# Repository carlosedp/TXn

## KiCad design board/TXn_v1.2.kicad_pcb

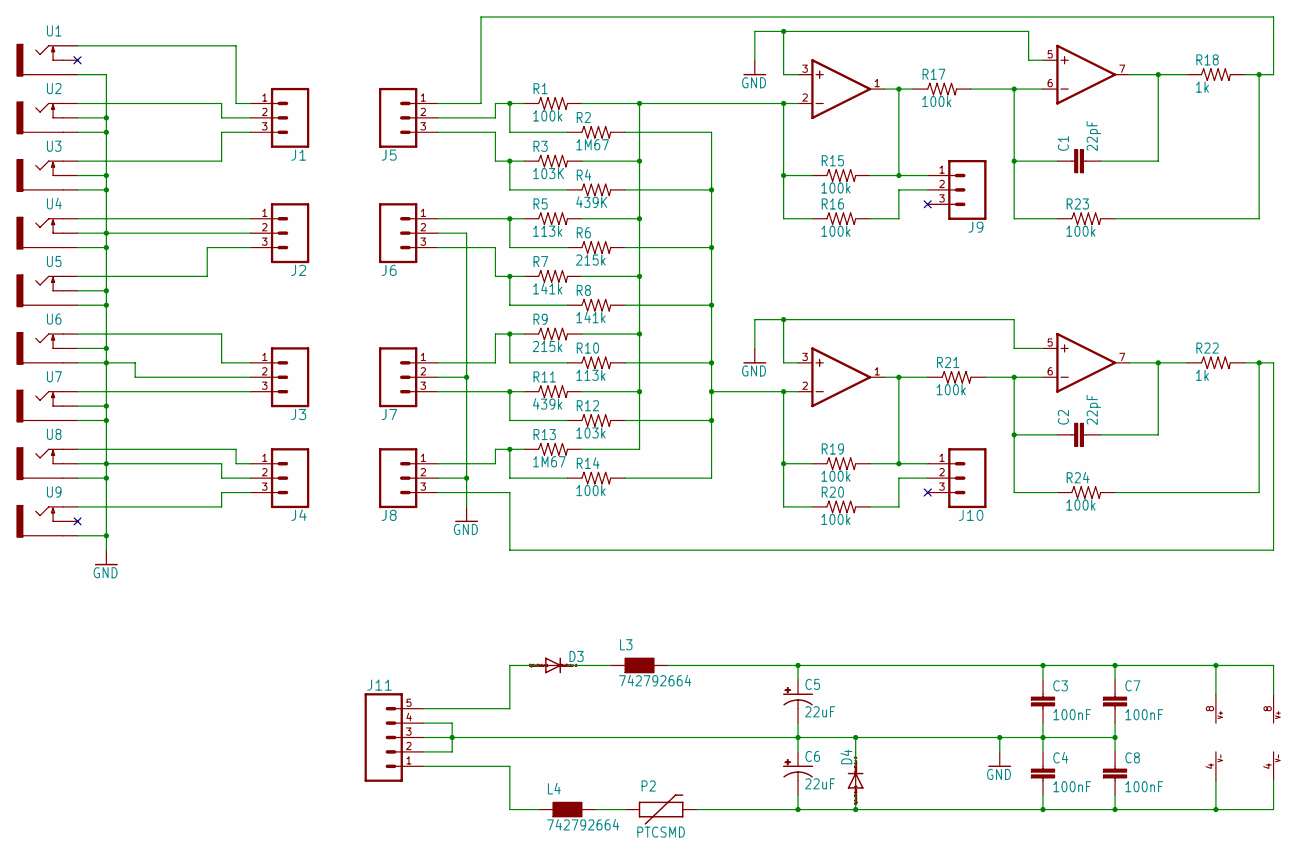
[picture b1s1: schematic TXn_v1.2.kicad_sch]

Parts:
C1, C2: 22pF; 0603-CAP
C3, C4, C7, C8: 100nF; 0603-CAP
C5, C6: 22uF; PANASONIC_B
D3, D4: DIODE-SOD123; SOD123
IC1, IC2: LME49720; SO08
J1, J2, J3, J4, J5, J6, J7, J8, J9, J10: CONN_031X03_NO_SILK; 1X03_NO_SILK
J11: CONN_05NO_SILK; 1X05_NO_SILK
L3, L4: 742792664; 0603
P2: PTCSMD; PTC-1206
R1, R14, R15, R16, R17, R19, R20, R21, R23, R24: 100k; R0603
R2, R13: 1M67; R0603
R3: 103K; R0603
R4: 439K; R0603
R5, R10: 113k; R0603
R6, R9: 215k; R0603
R7, R8: 141k; R0603
R11: 439k; R0603
R12: 103k; R0603
R18, R22: 1k; R0603
U1, U2, U3, U4, U5, U6, U7, U8, U9: THONKICONNLEFT; WQP-PJ301M-12_JACK_L

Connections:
BMIX: IC2.2 (-IN), R2.2, R4.2, R6.2, R8.2, R10.2, R12.2, R14.2, R19.1, R20.1
BOUT: J8.3, R22.2, R24.2
GND: C3.2, C4.1, C5.-, C6.+, C7.2, C8.1, D4.C, IC1.3 (+IN), IC1.5 (+IN), IC2.3 (+IN), IC2.5 (+IN), J2.2, J3.2, J4.2, J6.2, J7.2, J8.2, J11.2, J11.3, J11.4, U1.P$3_SLEEVE (SLEEVE), U2.P$2_SWITCH (SWITCH), U2.P$3_SLEEVE (SLEEVE), U3.P$2_SWITCH (SWITCH), U3.P$3_SLEEVE (SLEEVE), U4.P$2_SWITCH (SWITCH), U4.P$3_SLEEVE (SLEEVE), U5.P$2_SWITCH (SWITCH), U5.P$3_SLEEVE (SLEEVE), U6.P$2_SWITCH (SWITCH), U6.P$3_SLEEVE (SLEEVE), U7.P$2_SWITCH (SWITCH), U7.P$3_SLEEVE (SLEEVE), U8.P$2_SWITCH (SWITCH), U8.P$3_SLEEVE (SLEEVE), U9.P$3_SLEEVE (SLEEVE)
unnamed: J1.1, U1.P$1_TIP (TIP)
unnamed: J5.2, R1.1, R2.1
unnamed: J5.3, R3.1, R4.1
unnamed: J6.1, R5.1, R6.1
unnamed: J6.3, R7.1, R8.1
unnamed: J7.3, R11.1, R12.1
unnamed: J8.1, R13.1, R14.1
unnamed: J7.1, R9.1, R10.1
unnamed: J4.3, U9.P$1_TIP (TIP)
unnamed: J4.1, U8.P$1_TIP (TIP)
unnamed: J1.2, U2.P$1_TIP (TIP)
unnamed: J1.3, U3.P$1_TIP (TIP)
unnamed: J2.1, U4.P$1_TIP (TIP)
unnamed: J2.3, U5.P$1_TIP (TIP)
unnamed: J3.3, U7.P$1_TIP (TIP)
unnamed: IC2.1 (OUT), J10.1, R19.2, R21.1
unnamed: J3.1, U6.P$1_TIP (TIP)
unnamed: C2.1, IC2.6 (-IN), R21.2, R24.1
unnamed: IC1.1 (OUT), J9.1, R15.2, R17.1
unnamed: C1.1, IC1.6 (-IN), R17.2, R23.1
unnamed: C2.2, IC2.7 (OUT), R22.1
unnamed: J9.2, R16.2
unnamed: C1.2, IC1.7 (OUT), R18.1
unnamed: J10.2, R20.2
unnamed: D3.C, L3.1
unnamed: L4.2, P2.1
TMIX: IC1.2 (-IN), R1.2, R3.2, R5.2, R7.2, R9.2, R11.2, R13.2, R15.1, R16.1
TOUT: J5.1, R18.2, R23.2
VCC: C3.1, C5.+, C7.1, IC1.8 (V+), IC2.8 (V+), L3.2
VCC1: D3.A, J11.5
VEE: C4.2, C6.-, C8.2, D4.A, IC1.4 (V-), IC2.4 (V-), P2.2
VEE1: J11.1, L4.1

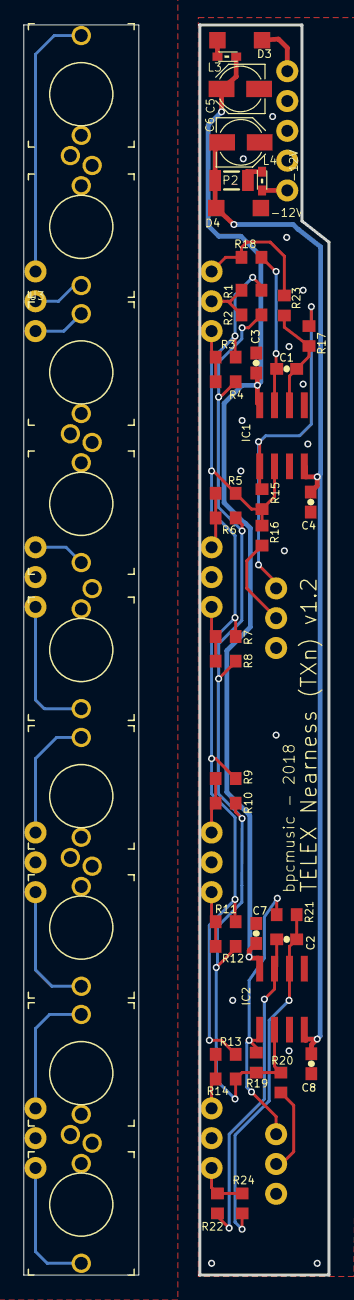
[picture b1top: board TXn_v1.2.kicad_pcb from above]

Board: 2 copper layers, 25.9 x 106.5 mm, 59 parts (0 on the bottom side), 35 nets.

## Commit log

2025-03-17 Add Kicad converted PCB and custom PCB panel

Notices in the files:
board/TXn_v1.2.kicad_pcb:
based on nearness by Jesper Särnesjö - CC BY-SA 4.0
